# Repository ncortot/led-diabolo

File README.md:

diabolo
=======

A tiny board for measurements and LED control on a Diabolo.

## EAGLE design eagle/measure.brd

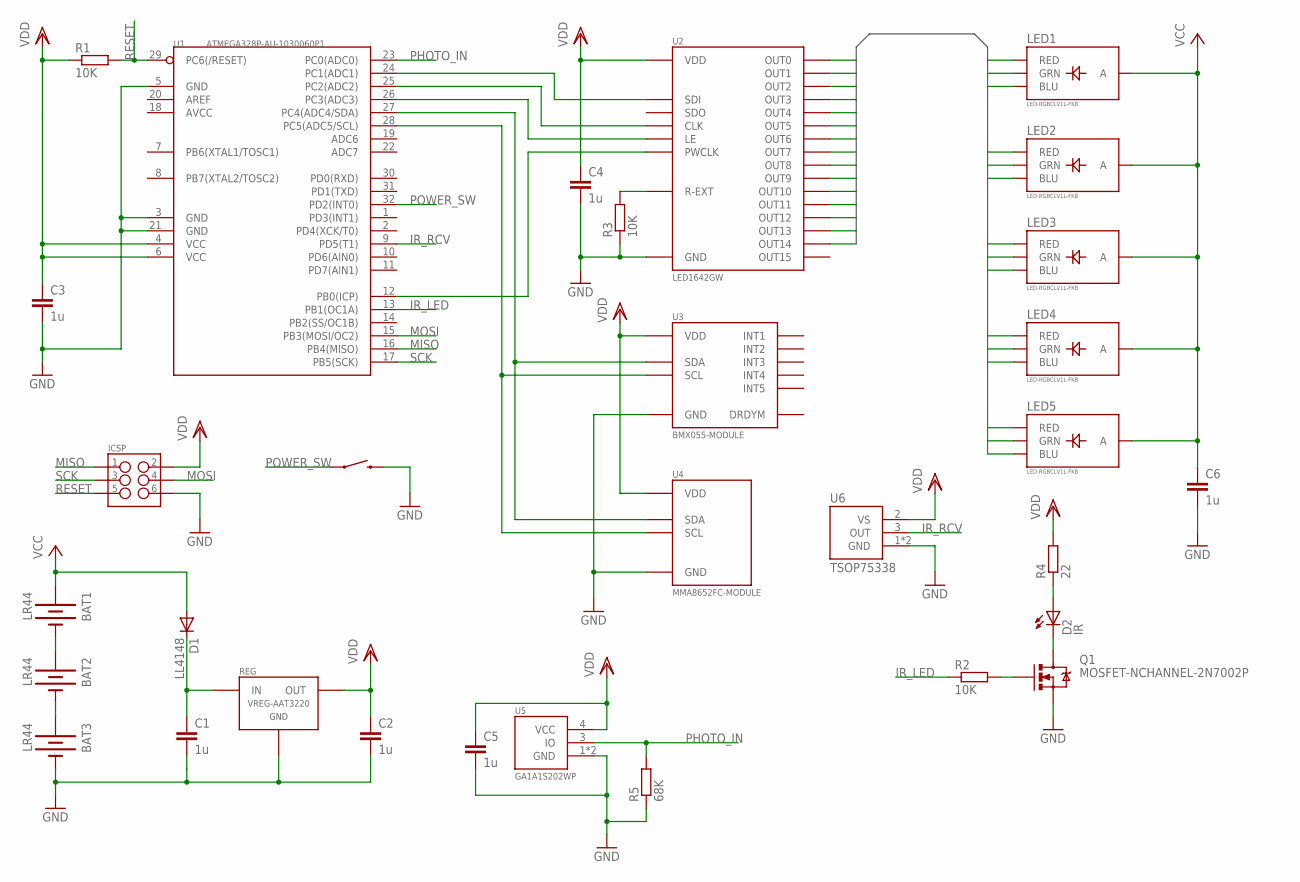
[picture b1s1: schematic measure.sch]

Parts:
BAT1, BAT2, BAT3: LR44; BATTERY_12MM_PTH
C1, C2, C3, C4, C5, C6: 1u; C0603
D1: LL4148; SOD80
D2: IR; LED-1206
ICSP: ICSP-HEADER; 2X3-ICSP
LED1, LED2, LED3, LED4, LED5: LED-RGBCLV1L-FKB; LED-RGB-CLV1L-FKB
POWER: SWITCH-MOMENTARY-2SMD; TACTILE_SWITCH_SMD
Q1: MOSFET-NCHANNEL-2N7002P; SOT23
R1, R2, R3: 10K; R0603
R4: 22; R0603
R5: 68K; R0603
REG: VREG-AAT3220; SC59
U1: ATMEGA328P-AU-1030060P1; TQFP32
U2: LED1642GW; TSSOP24
U3: BMX055-MODULE; BREAKOUT-BBTECH-DIP-12
U4: MMA8652FC-MODULE; BREAKOUT-BBTECH-DIP-12
U5: GA1A1S202WP
U6: TSOP75338; HEIMDALL-TOP

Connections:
GND: BAT3.GND (-), C1.2, C2.2, C3.2, C4.2, C5.2, C6.2, ICSP.6, POWER.3 (2), Q1.2 (S), R3.1, R5.1, REG.1 (GND), U1.3 (GND), U1.5 (GND), U1.21 (GND), U2.1 (GND), U3.P$1 (GND), U4.P$1 (GND), U5.1 (GND), U5.2 (GND), U6.1 (GND), U6.4 (GND)
IR_LED: R2.1, U1.13 (PB1(OC1A))
IR_RCV: U1.9 (PD5(T1)), U6.3 (OUT)
LED0: LED1.2 (RED), U2.5 (OUT0)
LED1: LED1.3 (GRN), U2.6 (OUT1)
LED2: LED1.4 (BLU), U2.7 (OUT2)
LED3: LED2.2 (RED), U2.8 (OUT3)
LED4: LED2.3 (GRN), U2.9 (OUT4)
LED5: LED2.4 (BLU), U2.10 (OUT5)
LED6: LED3.2 (RED), U2.11 (OUT6)
LED7: LED3.3 (GRN), U2.12 (OUT7)
LED8: LED3.4 (BLU), U2.13 (OUT8)
LED9: LED4.2 (RED), U2.14 (OUT9)
LED10: LED4.3 (GRN), U2.15 (OUT10)
LED11: LED4.4 (BLU), U2.16 (OUT11)
LED12: LED5.2 (RED), U2.17 (OUT12)
LED13: LED5.3 (GRN), U2.18 (OUT13)
LED14: LED5.4 (BLU), U2.19 (OUT14)
MISO: ICSP.1, U1.16 (PB4(MISO))
MOSI: ICSP.4, U1.15 (PB3(MOSI/OC2))
unnamed: U1.27 (PC4(ADC4/SDA)), U3.P$3 (SDA), U4.P$3 (SDA)
unnamed: U1.28 (PC5(ADC5/SCL)), U3.P$4 (SCL), U4.P$4 (SCL)
unnamed: U1.12 (PB0(ICP)), U2.21 (PWCLK)
unnamed: U1.24 (PC1(ADC1)), U2.2 (SDI)
unnamed: U1.25 (PC2(ADC2)), U2.3 (CLK)
unnamed: U1.26 (PC3(ADC3)), U2.4 (LE)
unnamed: R3.2, U2.23 (R-EXT)
unnamed: BAT1.GND (-), BAT2.VCC@1 (+), BAT2.VCC@2 (+)
unnamed: BAT2.GND (-), BAT3.VCC@1 (+), BAT3.VCC@2 (+)
unnamed: C1.1, D1.C, REG.3 (IN)
unnamed: D2.A, R4.1
unnamed: D2.C, Q1.3 (D)
unnamed: Q1.1 (G), R2.2
PHOTO_IN: R5.2, U1.23 (PC0(ADC0)), U5.3 (IO)
POWER_SW: POWER.1, U1.32 (PD2(INT0))
RESET: ICSP.5, R1.2, U1.29 (PC6(/RESET))
SCK: ICSP.3, U1.17 (PB5(SCK))
VCC: BAT1.VCC@1 (+), BAT1.VCC@2 (+), C6.1, D1.A, LED1.1 (A), LED2.1 (A), LED3.1 (A), LED4.1 (A), LED5.1 (A)
VDD: C2.1, C3.1, C4.1, C5.1, ICSP.2, R1.1, R4.2, REG.2 (OUT), U1.4 (VCC), U1.6 (VCC), U2.24 (VDD), U3.P$2 (VDD), U4.P$2 (VDD), U5.4 (VCC), U6.2 (VS)

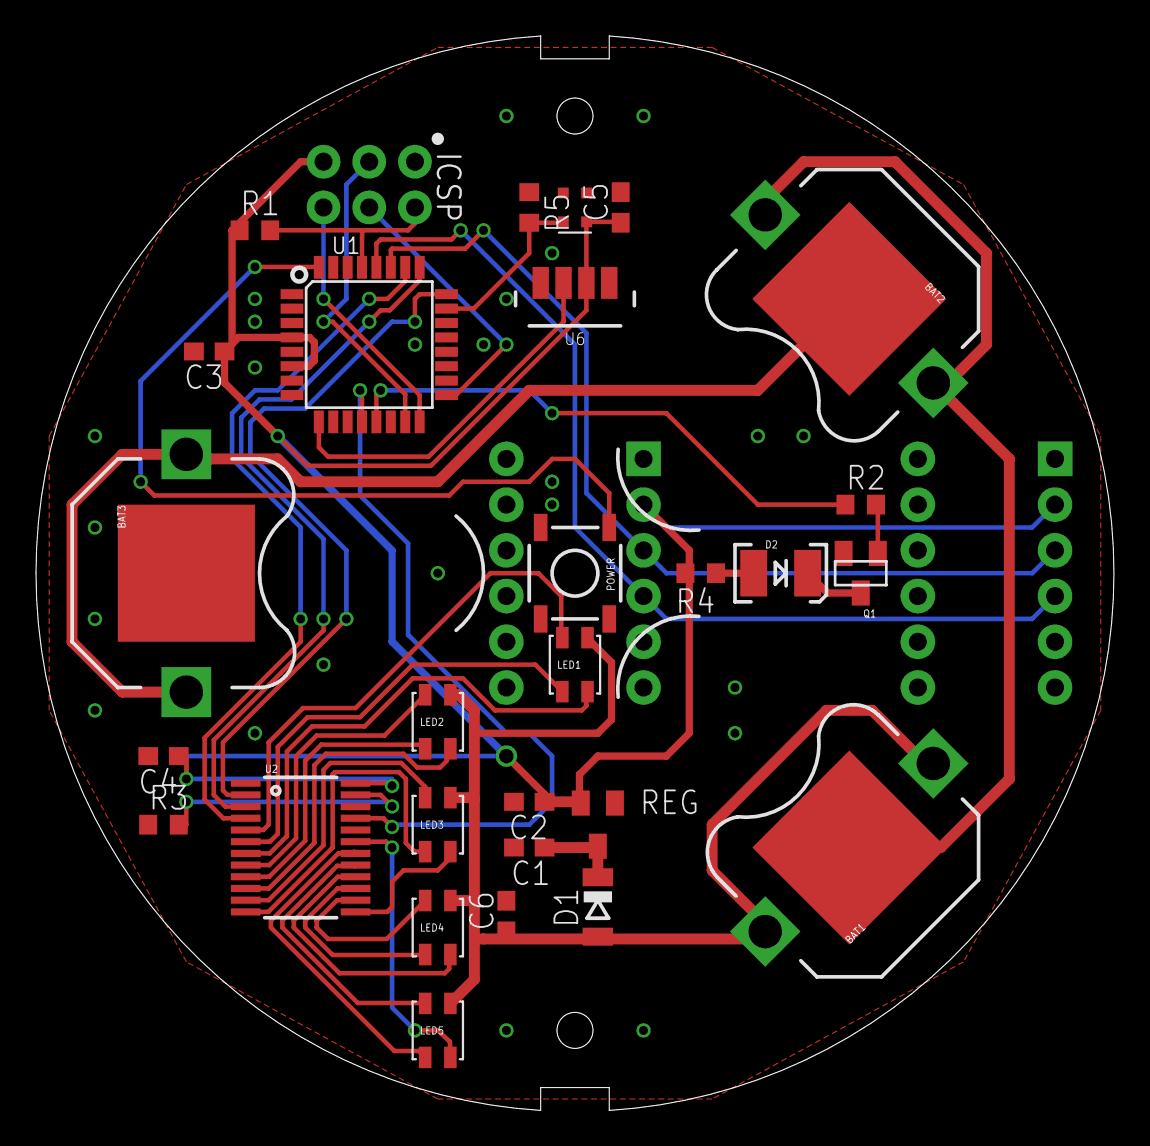
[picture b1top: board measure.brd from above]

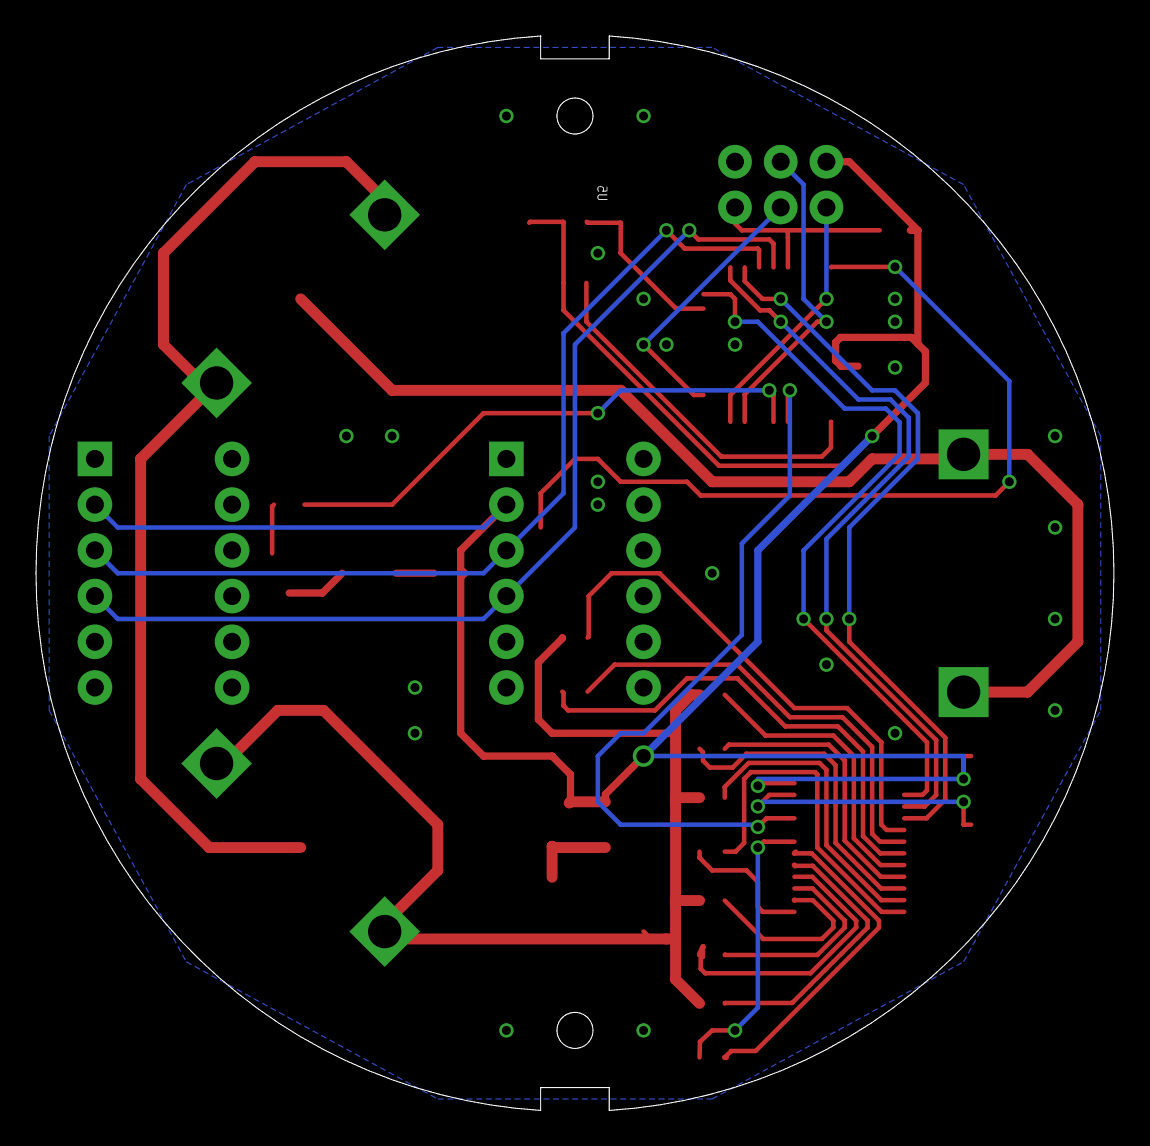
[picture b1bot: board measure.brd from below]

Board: 2 copper layers, 59.9 x 59.7 mm, 31 parts (2 on the bottom side), 39 nets.

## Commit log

2014-04-15 Eagle schematics
2014-04-15 Adding ATMEGA328P to the library
2014-04-15 Adding ADXL362 breakout
2014-04-15 Add batteries
2014-04-15 Add a pushbutton
2014-04-15 More connexions
2014-04-15 Minor update
2014-04-15 Adding PDFs
2014-04-16 Adding more components
2014-04-21 Bootstrap core board program
2014-04-21 Add programmer board code
2014-04-21 Rename packages
2014-04-22 Buind environment for Arduino
2014-04-22 Add a serial monitor
2014-06-09 LED driver test code
2014-06-09 LED1642GW setup using timer 2
2014-06-10 LED configuration fix
2014-06-10 Simple color demo
2014-06-10 Typo
2014-08-02 Cross-platform Makefile update
2014-08-02 Adding IRLib
2014-08-02 IR testing code
2014-08-03 Better Makefile configuration
2014-08-03 Remove AVR ISP programmer code
    This is not directly a part of the project, you can use any programmer.
    The Teensy 3.x AVR ISP programmer codebase can be found at:
    https://github.com/ncortot/teensy-avr-isp
2014-08-03 Skeleton for the receiver project
2014-08-03 Power the IR receiver directly through the ATMEGA pins
2014-08-03 Simpler serial monitor running
2014-08-03 Move remote commands definition to remote.h
2014-08-03 Serial monitor at 115200bps
2014-08-03 Use the clock output on PB0 for the led driver PWM clock
2014-08-03 IR commands debug
2014-08-16 Schematic update
2014-08-18 Schematics update with more components
2014-08-23 Board layout
2014-08-23 Adding more vias for GND
2014-08-24 Board update
2014-08-24 Adding Gerber files archive
2014-08-24 Parts library cleanup
2014-08-25 Power ON/OFF button handling
2014-08-25 Put the LED driver in auto power shutdown when sleeping
2015-08-10 Repo reorganization
2015-08-10 Code update
2015-08-10 Kicad project for the main board v2
2015-08-10 Move batteries to the bottom of the main board
2015-08-10 Power supply stages update
2015-08-11 Main board update
2015-08-11 Adding stacking connections
2015-08-11 Schematic fixes
2015-08-11 Schematic reorganization
2015-08-12 Add jumper footprints
2015-08-12 Update some libraries
2015-08-12 Use 02x12 2mm pitch headers
2015-08-12 Missing 2mm headers footprint
2015-08-12 Add some components
2015-08-13 Use standard 0603 LEDs
2015-08-13 Small fixes
2015-08-14 Fix some footprints
2015-08-15 Components update
2015-08-16 Remove silkscreen around PTH
2015-08-16 Placing components
2015-08-16 Routing
2015-08-17 More routing
2015-08-23 Main board routing
2015-09-01 Add version information
2015-09-01 Adding fab files
2015-09-01 Export config
2015-09-01 LED board layout
2015-09-01 Adding schematic PDF
2015-09-01 Adding 2mm pin headers
2015-09-01 LED board outline
2015-09-01 Outline fix
2015-09-05 Adding LED1642GW LED driver
2015-09-05 Add 5 RGB LEDs
2015-09-06 LED board update

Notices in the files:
parts and their libraries:
SparkFun-Electromechanical: Licensing: CC v3.0 Share-Alike You are welcome to use this library for commercial purposes.
